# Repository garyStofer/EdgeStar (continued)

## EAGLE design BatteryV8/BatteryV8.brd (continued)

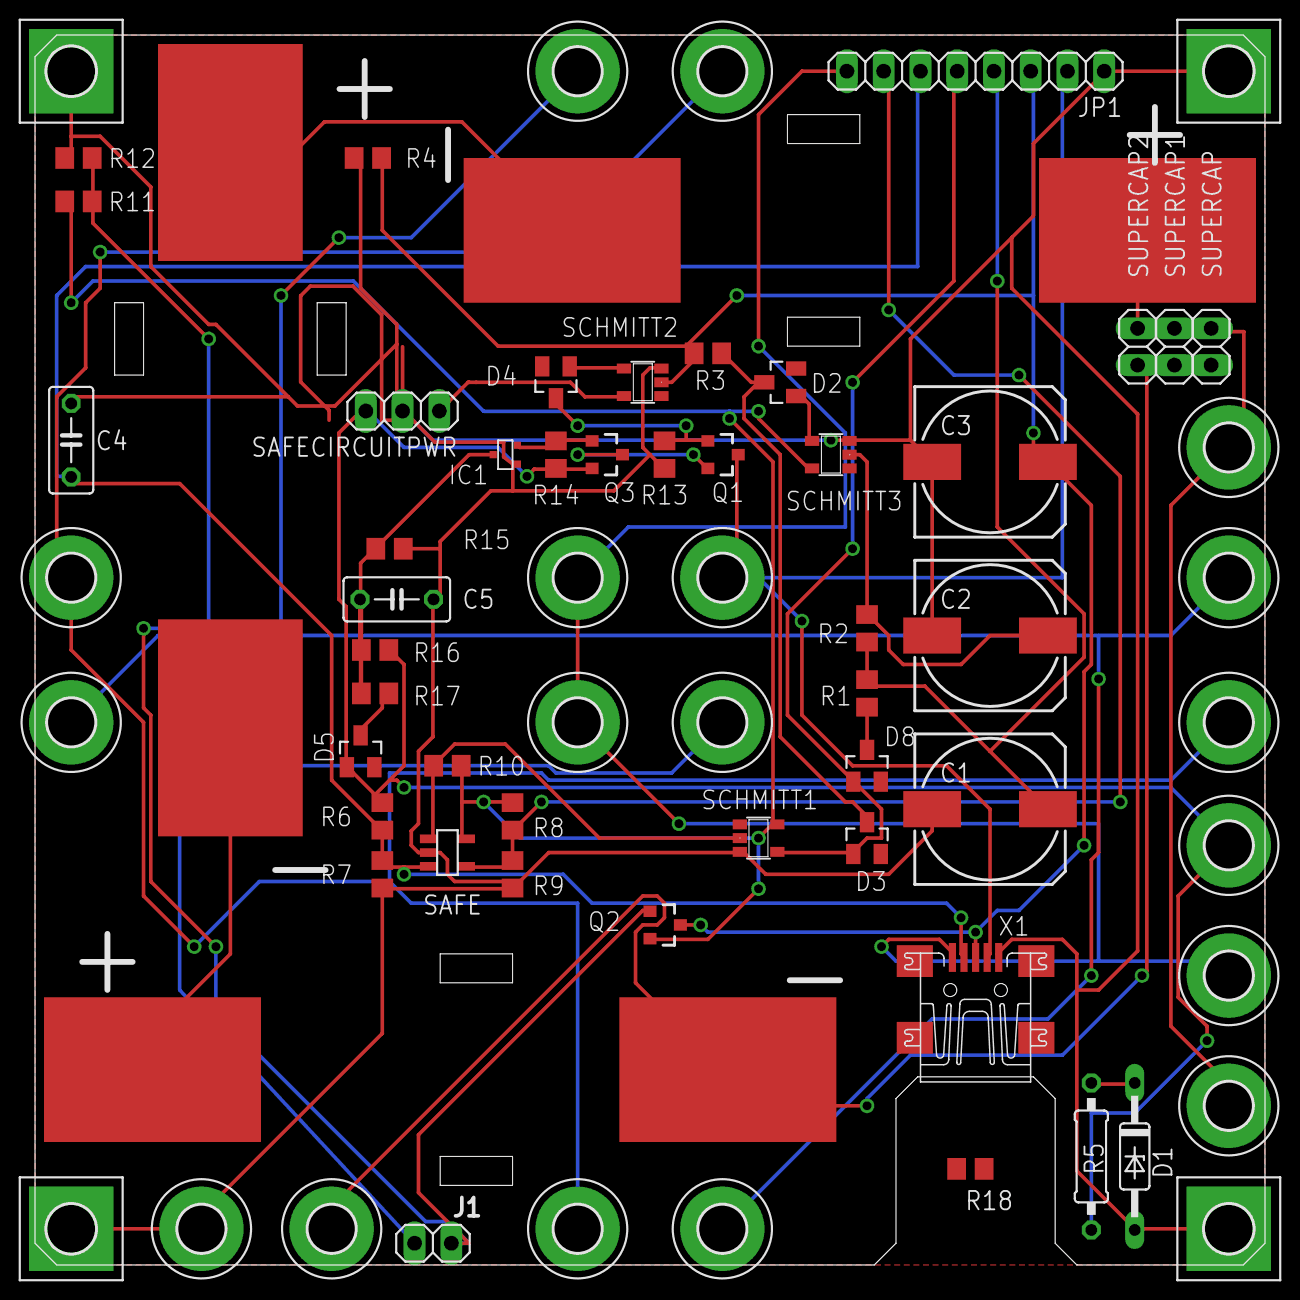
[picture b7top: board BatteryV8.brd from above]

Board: 2 copper layers, 85.0 x 85.0 mm, 69 parts (0 on the bottom side), 30 nets.

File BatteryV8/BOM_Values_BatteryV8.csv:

Qty; Value;               Device;               Package;        Parts;                        DIGIKEY;       TOPMARK;
1;   100u,16V,elec,rad ;   C-US050-030X075  ;    C050-030X075 ;  C4                        ;399-6648-1-ND;              ;
1;   10uf,50V,elec,rad ;   C-US050-030X075  ;    C050-030X075  ; C5   Value discrepancy    ;P807-ND ;              ; 
1 ;  120K              ;   R-US_0207/10     ;    0207/10      ;  R18                       ;               ;              ; 
1;   120K              ;   R-US_M0805       ;    M0805        ;  R6                        ;               ;              ; 
1;   180K              ;   R-US_M0805        ;   M0805        ;  R4                        ;                ;              ;
3;   220               ;   R-US_M0805       ;    M0805        ;  R1, R2, R3                ;               ;               ;
1;   220K              ;   R-US_M0805       ;    M0805        ;  R11                       ;                ;             ; 
1;   270K              ;   R-US_M0805       ;    M0805        ;  R10                       ;                ;             ; 
1;   390K              ;   R-US_M0805       ;    M0805        ;  R7                        ;                ;             ; 
1;   47mF,5.5V         ;   CPOL-US153CLV-1010;   153CLV-1010  ;  C1,C3                     ; 399-16033-1ND  ;             ;    
5;   560K              ;   R-US_M0805        ;   M0805        ;  R8, R9, R13, R14, R16     ;                ;             ; 
3;   74AUC1G14DBV      ;   74AUC1G14DBV      ;   SOT23-5      ;  SCHMITT1, SCHMITT2, SCHMITT3 ; 296-12880-1-ND;       C175  ; 
3 ;  AA-BATT           ;   Nicad-AA-BATT     ;   AA-BATT      ;  U$5, U$6, U$7               ;              ;             ; 
3;   BAS40             ;   BAS40             ;   SOT23        ;  D2, D4, D8                  ;BAS40-04fdict-ND;       88Y   ; 
1;   INA138            ;   INA138            ;   SOT23-5      ;  SAFE                        ;296-17936-1-ND;       15F2  ; 
1;   MAX6465XR29T      ;   MAX6465           ;   SC70-3       ;  IC1                         ;MAX6465XR27+TCT-ND;       AMW   ; 
3;   MOSFET-PCHANNEL   ;   MOSFET-PCHANNEL   ;   SOT23-3      ;  Q1, Q2, Q3                  ; SSM3J338RLFCT-ND;       KFQ   ; 
1;   Pololu 5V, S10V4F5;   M03PTH            ;   1X03         ;  SAFECIRCUITPOWER            ; 2183-2121-ND ;             ; 
1;Pinheader straight 0.1; 					;		1x8 0.1;	;JP1						; S1011EC-8-ND	;				;
1;   NP                ;   1N821             ;   DO35Z10      ;  D1                          ;              ;             ; 
2;   NP                ;   BAS40             ;   SOT23        ;  D3, D5                      ;              ;              ;
1;   NP                ;   CPOL-US153CLV-1010;   153CLV-1010  ;  C2                          ;              ;             ; 
1;   NP                ;   R-US_0207/10      ;   0207/10      ;  R5                          ;              ;             ; 
3;   NP                ;   R-US_M0805        ;   M0805        ;  R12, R15, R17               ;              ;             ;

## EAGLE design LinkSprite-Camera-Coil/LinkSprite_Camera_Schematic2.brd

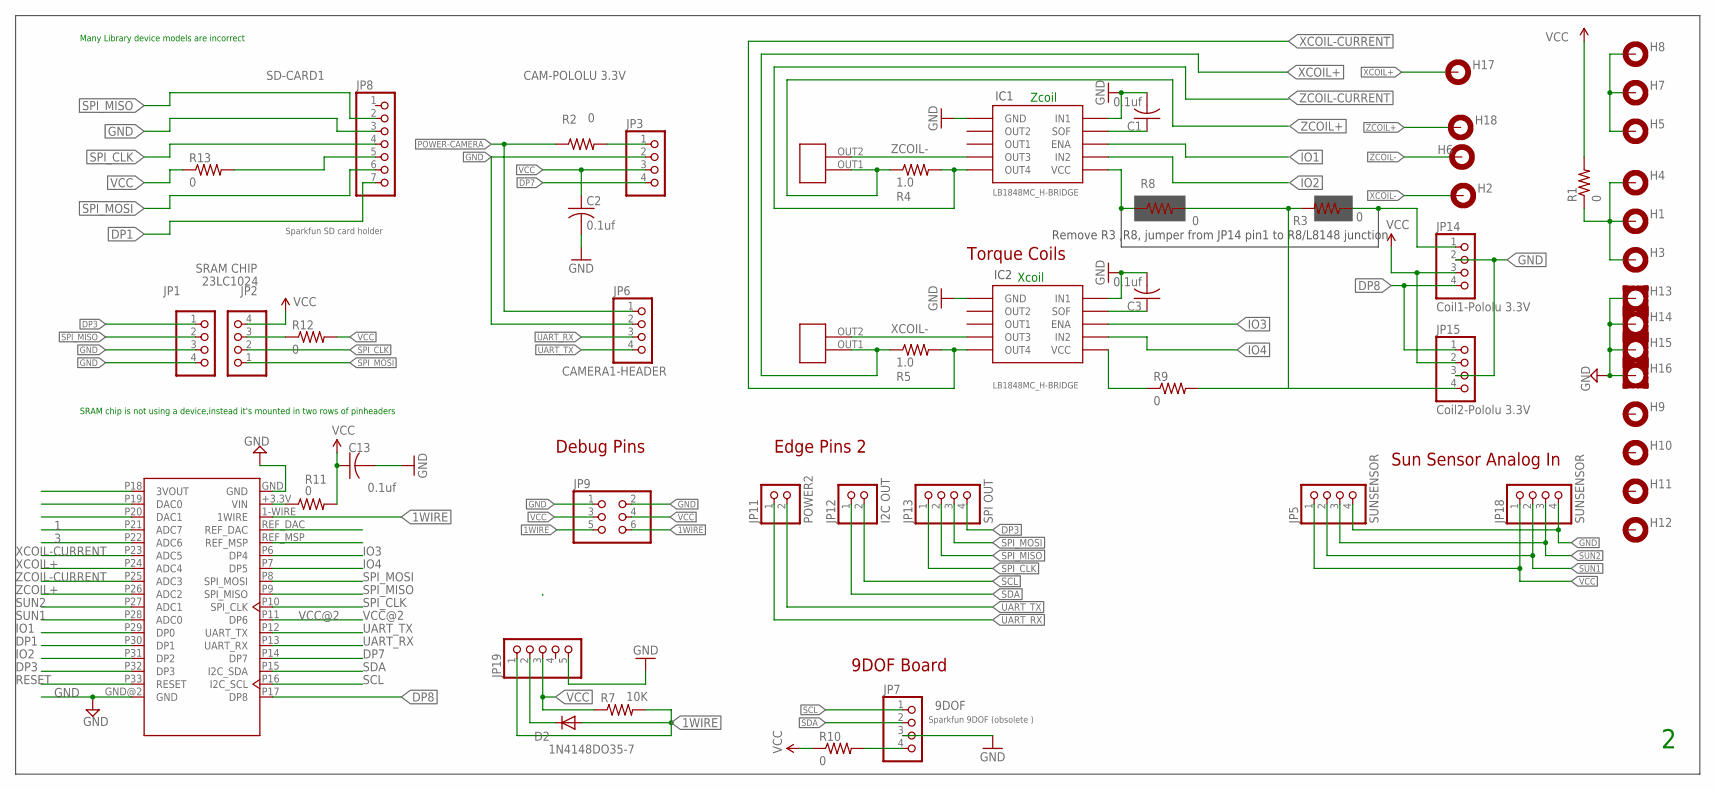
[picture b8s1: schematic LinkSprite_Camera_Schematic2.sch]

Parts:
C1, C3: 0.1uf; C1206
C2, C13: 0.1uf; C0805
D2: 1N4148DO35-7; DO35-7
H1, H2, H3, H4, H5, H6, H7, H8, H9, H10, H11, H12, H17, H18: MOUNT-PAD-ROUND3.3; 3,3-PAD
H13, H14, H15, H16: MOUNT-PAD-SQUARE3.3; 3,3-PAD-SQUARE
IC1, IC2: LB1848MC_H-BRIDGE; DIGI_KEY LB1848MC-AHOSCT-ND
JP1: SRAMLEFT; 1X04
JP2: 23LC1024; 1X04; DIGI-KEY 23LC1024-I/P-ND
JP3: CAM-POLOLU 3.3V; 1X04
JP5, JP18: SUNSENSOR; 1X04
JP6: CAMERA1-HEADER; 1X04; DIGIKEY SAM10018-ND
JP7: 9DOF; 1X04
JP8: SD-CARD1; 1X07
JP9: PINHD-2X3; 2X03
JP11: POWER2; 1X02
JP12: I2C OUT; 1X02
JP13: SPI OUT; 1X04
JP14: Coil1-Pololu 3.3V; 1X04
JP15: Coil2-Pololu 3.3V; 1X04
JP19: PINHD-1X5; 1X05
R1, R3, R8, R9, R10, R11, R12, R13: 0; R0805
R2: 0; R0805; DIGI-KEY 311-0.0ARCT-ND
R4, R5: 1.0; R1206
R7: 10K; 0204/7
U$1: App-Board 1.2/1.3; APPCORE_RECEIVER
U$5, U$6: COIL_PINOUT

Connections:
1: U$1.P21 (ADC7)
1WIRE: D2.A, H5.B3,3, H7.B3,3, H8.B3,3, JP9.5, JP9.6, JP19.1, R7.2, U$1.1-WIRE (1WIRE)
3: U$1.P22 (ADC6)
COIL-POWER: JP15.4, R3.2, R8.2, R9.2
DP1: JP8.7, U$1.P30 (DP1)
DP3: JP1.1, JP13.4, U$1.P32 (DP3)
DP7: JP3.4, U$1.P14 (DP7)
DP8: JP14.4, JP15.1, U$1.P17 (DP8)
GND: C1.2, C2.2, C3.2, C13.2, H13.B3,3, H14.B3,3, H15.B3,3, H16.B3,3, IC1.GND, IC1.IN1, IC2.GND, IC2.IN1, JP1.3, JP1.4, JP3.2, JP5.4, JP6.2, JP7.3, JP8.3, JP9.1, JP9.2, JP14.2, JP15.3, JP18.4, JP19.5, U$1.GND, U$1.GND@2 (GND)
IO1: IC1.ENA, U$1.P29 (DP0)
IO2: IC1.IN2, U$1.P31 (DP2)
IO3: IC2.ENA, U$1.P6 (DP4)
IO4: IC2.IN2, U$1.P7 (DP5)
unnamed: JP14.1, R3.1
unnamed: H1.B3,3, H3.B3,3, H4.B3,3, R1.1
unnamed: JP3.1, R2.2
unnamed: IC1.VCC, R8.1
unnamed: IC2.VCC, R9.1
unnamed: JP7.4, R10.2
unnamed: D2.C, JP19.2
unnamed: R11.1, U$1.+3.3V (VIN)
unnamed: C3.1, IC2.SOF
unnamed: C1.1, IC1.SOF
unnamed: JP2.3, R12.1
unnamed: JP8.5, R13.2
POWER-CAMERA: JP6.1, R2.1
RESET: U$1.P33 (RESET)
SCL: JP7.1, JP12.2, U$1.P16 (I2C_SCL)
SDA: JP7.2, JP12.1, U$1.P15 (I2C_SDA)
SPI_CLK: JP2.2, JP8.4, JP13.1, U$1.P10 (SPI_CLK)
SPI_MISO: JP1.2, JP8.2, JP13.2, U$1.P9 (SPI_MISO)
SPI_MOSI: JP2.1, JP8.6, JP13.3, U$1.P8 (SPI_MOSI)
SUN1: JP5.2, JP18.2, U$1.P28 (ADC0)
SUN2: JP5.3, JP18.3, U$1.P27 (ADC1)
UART_RX: JP6.3, JP11.1, U$1.P13 (UART_RX)
UART_TX: JP6.4, JP11.2, U$1.P12 (UART_TX)
VCC: C2.1, C13.1, JP2.4, JP3.3, JP5.1, JP9.3, JP9.4, JP14.3, JP15.2, JP18.1, JP19.3, R1.2, R7.1, R10.1, R11.2, R12.2, R13.1
VCC@2: U$1.P11 (DP6)
XCOIL+: H17.B3,3, R5.1, U$1.P24 (ADC4), U$6.OUT1
XCOIL-: H2.B3,3, IC2.OUT3, U$6.OUT2
XCOIL-CURRENT: IC2.OUT4, R5.2, U$1.P23 (ADC5)
ZCOIL+: H18.B3,3, R4.1, U$1.P26 (ADC2), U$5.OUT1
ZCOIL-: H6.B3,3, IC1.OUT3, U$5.OUT2
ZCOIL-CURRENT: IC1.OUT4, R4.2, U$1.P25 (ADC3)

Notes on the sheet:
SRAM CHIP
Zcoil
Xcoil
Edge Pins 2
Sun Sensor Analog In
9DOF Board
Debug Pins
Torque Coils
Many Library device models are incorrect
SRAM chip is not using a device,instead it's mounted in two rows of pinheaders
LB1848MC_H-BRIDGE
Sparkfun SD card holder
Sparkfun 9DOF (obsolete )
Remove R3 ,R8, jumper from JP14 pin1 to R8/L8148 junction
IC1
IC2

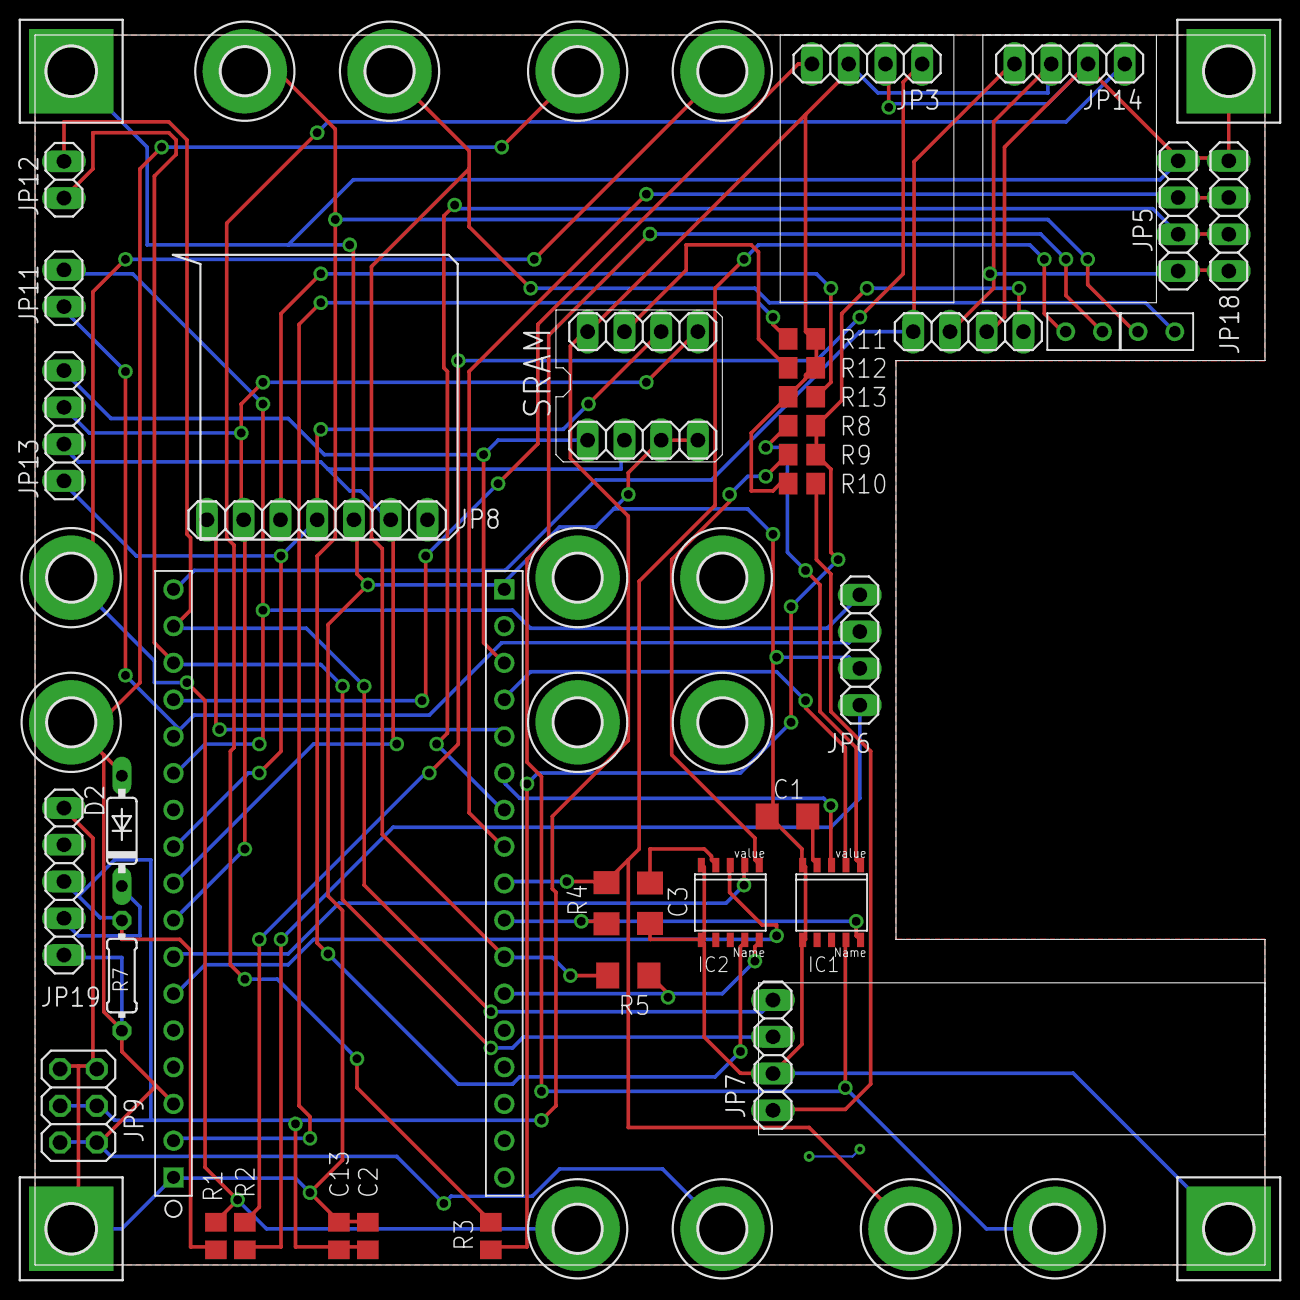
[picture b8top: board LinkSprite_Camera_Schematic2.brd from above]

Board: 2 copper layers, 85.0 x 85.0 mm, 55 parts (0 on the bottom side), 40 nets.

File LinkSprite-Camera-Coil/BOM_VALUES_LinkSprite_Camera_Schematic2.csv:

"Qty";"Value";"Device";"Package";"Parts";"Description";"DIGI-KEY";"DIGI_KEY";
"1";"";"PINHD-1X5";"1X05";"JP19";"PIN HEADER";"";"";
"1";"";"PINHD-2X3";"2X03";"JP9";"PIN HEADER";"";"";
"1";"0";"R-US_R0805";"R0805";"R2";"RESISTOR, American symbol";"311-0.0ARCT-ND";"";
"8";"0";"R-US_R0805";"R0805";"R1, R3, R8, R9, R10, R11, R12, R13";"RESISTOR, American symbol";"";"";
"2";"0.1uf";"C-USC0805";"C0805";"C2, C13";"CAPACITOR, American symbol";"";"";
"2";"0.1uf";"C-USC1206";"C1206";"C1, C3";"CAPACITOR, American symbol";"";"";
"2";"1.0";"R-US_R1206";"R1206";"R4, R5";"RESISTOR, American symbol";"";"";
"1";"10K";"R-US_0204/7";"0204/7";"R7";"RESISTOR, American symbol";"";"";
"1";"1N4148DO35-7";"1N4148DO35-7";"DO35-7";"D2";"DIODE";"";"";
"1";"23LC1024";"PINHD-1X4";"1X04";"JP2";"PIN HEADER";"23LC1024-I/P-ND";"";
"1";"9DOF";"PINHD-1X4";"1X04";"JP7";"PIN HEADER";"";"";
"1";"App-Board 1.2/1.3";"APP_CORE";"APPCORE_RECEIVER";"U$1";"";"";"";
"1";"CAM-POLOLU 3.3V";"PINHD-1X4";"1X04";"JP3";"PIN HEADER";"";"";
"1";"CAMERA1-HEADER";"PINHD-1X4";"1X04";"JP6";"PIN HEADER";"";"";
"2";"COIL_PINOUT";"COIL_PINOUT";"COIL_PINOUT";"U$5, U$6";"";"";"";
"1";"Coil1-Pololu 3.3V";"PINHD-1X4";"1X04";"JP14";"PIN HEADER";"";"";
"1";"Coil2-Pololu 3.3V";"PINHD-1X4";"1X04";"JP15";"PIN HEADER";"";"";
"1";"I2C OUT";"PINHD-1X2";"1X02";"JP12";"PIN HEADER";"";"";
"2";"LB1848MC_H-BRIDGE";"LB1848MC_H-BRIDGE";"LB1848MC_H-BRIDGE";"IC1, IC2";"";"";"LB1848MC-AHOSCT-ND";
"14";"MOUNT-PAD-ROUND3.3";"MOUNT-PAD-ROUND3.3";"3,3-PAD";"H1, H2, H3, H4, H5, H6, H7, H8, H9, H10, H11, H12, H17, H18";"MOUNTING PAD, round";"";"";
"4";"MOUNT-PAD-SQUARE3.3";"MOUNT-PAD-SQUARE3.3";"3,3-PAD-SQUARE";"H13, H14, H15, H16";"MOUNTING PAD, square";"";"";
"1";"POWER2";"PINHD-1X2";"1X02";"JP11";"PIN HEADER";"";"";
"1";"SD-CARD1";"PINHD-1X7";"1X07";"JP8";"PIN HEADER";"";"";
"1";"SPI OUT";"PINHD-1X4";"1X04";"JP13";"PIN HEADER";"";"";
"1";"SRAMLEFT";"PINHD-1X4";"1X04";"JP1";"PIN HEADER";"";"";
"2";"SUNSENSOR";"PINHD-1X4";"1X04";"JP5, JP18";"PIN HEADER";"";"";

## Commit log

2019-12-04 added battery PCB
2019-12-05 added hours file
2019-12-05 included the wrong hours file -- using spreadsheet
2019-12-05 Deleted eagle temp files
2019-12-06 updated schematics and BOM with notes in the course of assembling the 3 main PCBs
2020-07-13 Modified schematic and BOM to represent actual board - Smitt triggers. Extracted library elements from schematic and created two local libraries with all the non standard or modified elements used on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
2020-07-13 Added more to the Circuit description
2020-08-14 added V0.1 of Battery Monitor test board.
2020-10-22 New Schematic and Layout for Battery controller added
2020-10-22 cleaned up Eagle.EPF FILE
2020-10-22 added uStar Version 2.0 PCB and schematic
2020-10-22 added first version of Gerber file zip as manufactured
2020-12-17 Added the cost of parts and Labor in the BOM
2020-12-17 added the 3D parts to the library added cost and hours to the BOM
2020-12-17 Added 3D elements to local lib
2021-04-22 first add of bmx160 board
2021-04-22 initial addition of TorqueCoils
2021-12-15 change in BOM file -- small silkscreen change on PCB
2021-12-15 Changed solder stop mask to fully cover vias to protect from short with RFM23bp. Changed brd rev label to 2.1b to reflect above. Added R9 and R11 back into the flight build - Inadvertently removed wh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
2021-12-15 First commit of App board u-logo/j-logo program set to exercise the uStar-V2 board with it's dual radios. Two projects, one for sending packets and one to receive and display them on the PC -- Projec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
2021-12-20 Added by Lynn: ADC readings added to the test package generation Corrected comments in mycommon.txt
2022-03-02 added files for app board
